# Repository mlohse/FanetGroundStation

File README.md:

# FanetGroundStation
A linux daemon for broadcasting weather data from the internet via FANET (requires Skytraxx FANET+ Module)

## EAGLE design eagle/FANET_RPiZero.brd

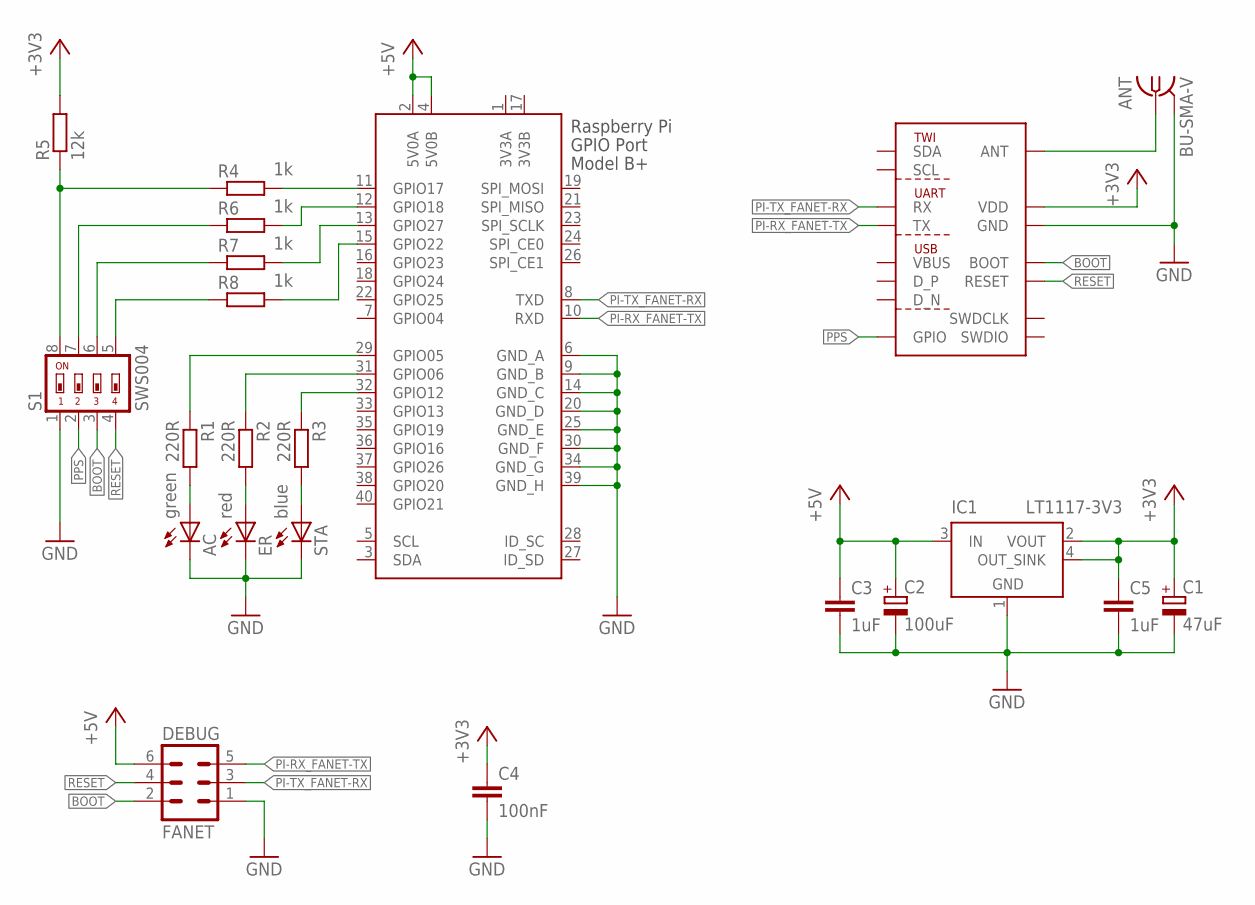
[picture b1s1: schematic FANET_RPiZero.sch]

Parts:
AC: green; CHIP-LED0805
ANT: BU-SMA-V
C1: 47uF; SMC_C
C2: 100uF; SMC_C
C3, C5: 1uF; C1206
C4: 100nF; C1206
DEBUG: FANET; ML6
ER: red; CHIP-LED0805
FANET_MODULE: FANET_MODULE; FANET_INTERNAL
IC1: LT1117-3V3; SOT223
R1, R2, R3: 220R; R0805
R4, R6, R7, R8: 1k; R0805
R5: 12k; R0805
RASPI_ZERO: RASPI_GPIO_B+#; RASPI_BOARD_ZERO_FULL_PAD
S1: SWS004; SMS-004
STA: blue; CHIP-LED0805

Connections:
3V3A: RASPI_ZERO.1 (3V3A)
3V3B: RASPI_ZERO.17 (3V3B)
+3V3: C1.+, C4.1, C5.1, FANET_MODULE.VSS (VDD), IC1.2 (VOUT), IC1.4 (OUT_SINK), R5.2
+5V: C2.+, C3.1, DEBUG.6, IC1.3 (IN), RASPI_ZERO.2 (5V0A), RASPI_ZERO.4 (5V0B)
BOOT: DEBUG.2, FANET_MODULE.BOOT, S1.3
GND: AC.C, ANT.2, ANT.3 (2), ANT.4 (2), ANT.5 (2), C1.-, C2.-, C3.2, C4.2, C5.2, DEBUG.1, ER.C, FANET_MODULE.GND0 (GND), FANET_MODULE.GND1 (GND), IC1.1 (GND), RASPI_ZERO.6 (GND_A), RASPI_ZERO.9 (GND_B), RASPI_ZERO.14 (GND_C), RASPI_ZERO.20 (GND_D), RASPI_ZERO.25 (GND_E), RASPI_ZERO.30 (GND_F), RASPI_ZERO.34 (GND_G), RASPI_ZERO.39 (GND_H), S1.1, STA.C
unnamed: ANT.1, FANET_MODULE.ANT
unnamed: R4.2, RASPI_ZERO.11 (GPIO17)
unnamed: R4.1, R5.1, S1.8
unnamed: R6.1, S1.7
unnamed: R6.2, RASPI_ZERO.12 (GPIO18)
unnamed: R7.2, RASPI_ZERO.13 (GPIO27)
unnamed: R8.2, RASPI_ZERO.15 (GPIO22)
unnamed: R7.1, S1.6
unnamed: R8.1, S1.5
unnamed: AC.A, R1.2
unnamed: ER.A, R2.2
unnamed: R3.2, STA.A
unnamed: R3.1, RASPI_ZERO.32 (GPIO12)
unnamed: R2.1, RASPI_ZERO.31 (GPIO06)
unnamed: R1.1, RASPI_ZERO.29 (GPIO05)
PI-RX_FANET-TX: DEBUG.5, FANET_MODULE.TX, RASPI_ZERO.10 (RXD)
PI-TX_FANET-RX: DEBUG.3, FANET_MODULE.RX, RASPI_ZERO.8 (TXD)
PPS: FANET_MODULE.GPIO0 (GPIO), S1.2
RESET: DEBUG.4, FANET_MODULE.RESET, S1.4

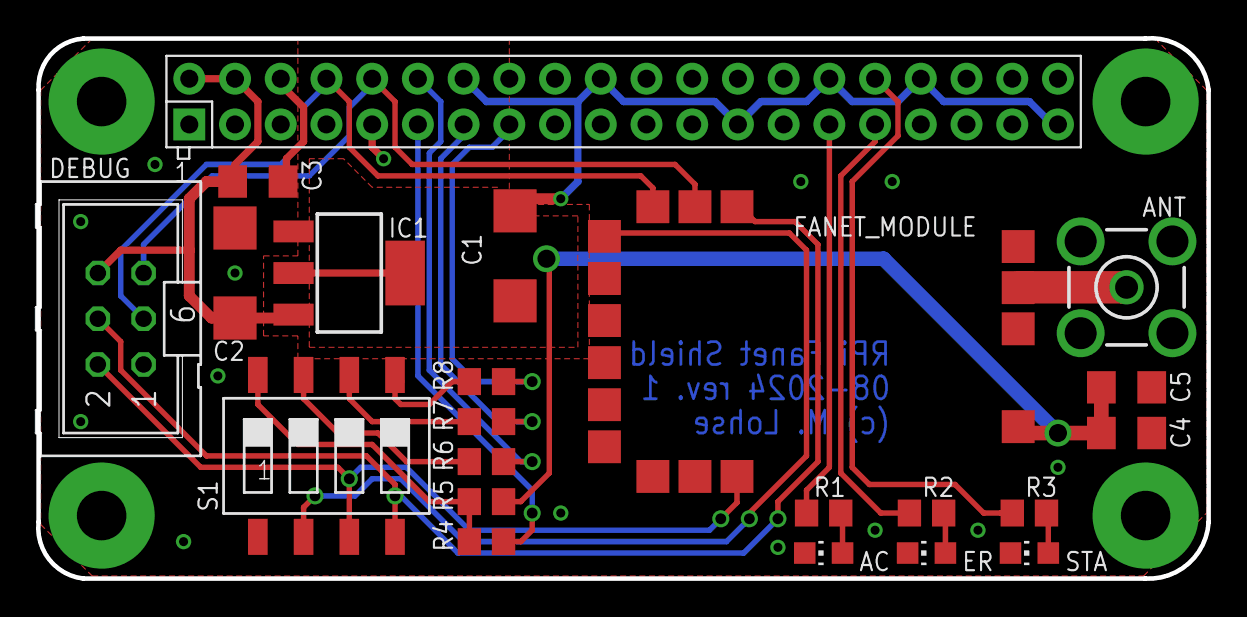
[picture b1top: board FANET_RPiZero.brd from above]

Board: 2 copper layers, 65.0 x 30.0 mm, 22 parts (0 on the bottom side), 23 nets.

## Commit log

2025-08-17 publish initial version 1.0.0
2025-08-17 add Eagle files for Raspberry Pi Zero shield
2025-08-30 add manufacturer id (Burnair)
